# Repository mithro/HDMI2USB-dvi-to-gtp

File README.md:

Circuit designs for allowing DVI/HDMI be received on the GTP transceivers
inside the Spartan 6 LXT series parts.

Based of the information in 
[Xilinx provided XAPP1007](http://www.xilinx.com/support/documentation/application_notes/xapp1077-phy-hdmi-rx-gtp.pdf)

Designed for use with [HDMI2USB firmware](http://github.com/timvideos/HDMI2USB)
on the prototype version of the [Numato](http://numato.com/) HDMI2USB
"Conference" board.

# Files

Design is done in [KiCad](http://www.kicad-pcb.org/) using version
0.201408302346+5106~15~ubuntu12.04.1 (IE Subversion revision 5106 packaged on
2014/08/30 for Ubuntu Precise LTS - 12.04.01).

 * `dvi-to-gtp.pro`         - KiCad project.

  * `dvi-to-gtp.sch`         - Schematic
   * `dvi-to-gtp-cache.lib`  - Cache of components in use
   * `dvi-d.lib`             - DVI-D connector

  * `dvi-to-gtp.cmp`         - parts-to-module assignments file

  * `dvi-to-gtp.kicad_pcb`   - PCB Design
   * `dvi-d.pretty`          - DVI-D connector
   * `fp-lib-table`          - PCB library look up path

# Components

DVI-D connector used is;
 * Molex 74320-9004 - DVI-D, Dual Link, Panel Mount, Through Hole, Right Angle - [Datasheet](http://www.molex.com/pdm_docs/sd/743209004_sd.pdf)
 * Purchased from [Digikey](http://www.digikey.com/product-search/en?KeyWords=WM6095-ND&WT.z_header=search_go)

Passives;
 * [587-2658-1-ND](http://www.digikey.com/product-detail/en/LK21251R0K-T/587-2658-1-ND/2350029) - INDUCTOR MULTILAYER 1UH 0805
 * [1276-1443-1-ND](http://www.digikey.com/product-detail/en/CL05A104MP5NNNC/1276-1443-1-ND/3889529) - CAP CER 0.1UF 10V 20% X5R 0402
 * [RHM51.0CDCT-ND](http://www.digikey.com/product-detail/en/MCR01MRTF51R0/RHM51.0CDCT-ND/2796435) - RES 51 OHM 1/16W 1% 0402 SMD

# License

Copyright 2014 Tim "mithro" Ansell

Licensed under the Apache License, Version 2.0 (the "License");
you may not use this file except in compliance with the License.
You may obtain a copy of the License at

    http://www.apache.org/licenses/LICENSE-2.0

Unless required by applicable law or agreed to in writing, software
distributed under the License is distributed on an "AS IS" BASIS,
WITHOUT WARRANTIES OR CONDITIONS OF ANY KIND, either express or implied.
See the License for the specific language governing permissions and
limitations under the License.

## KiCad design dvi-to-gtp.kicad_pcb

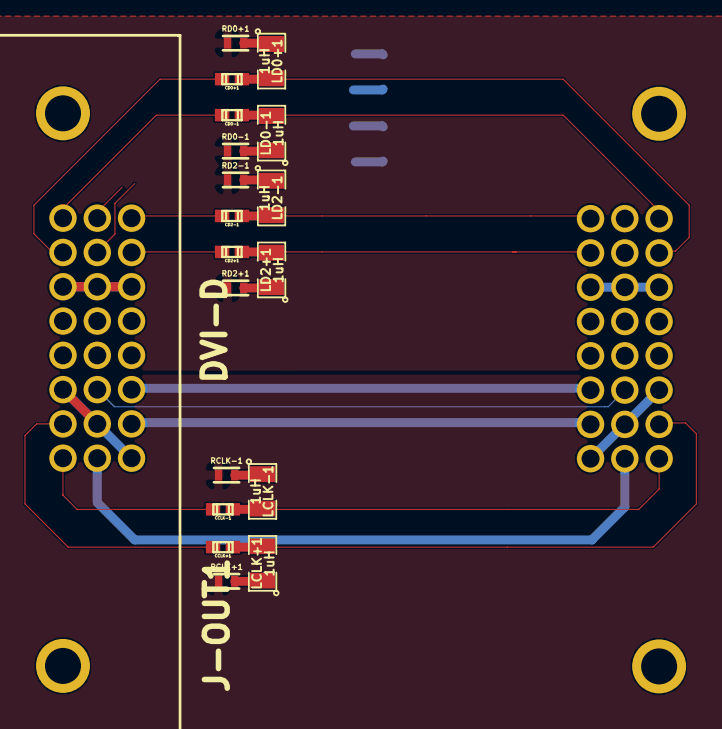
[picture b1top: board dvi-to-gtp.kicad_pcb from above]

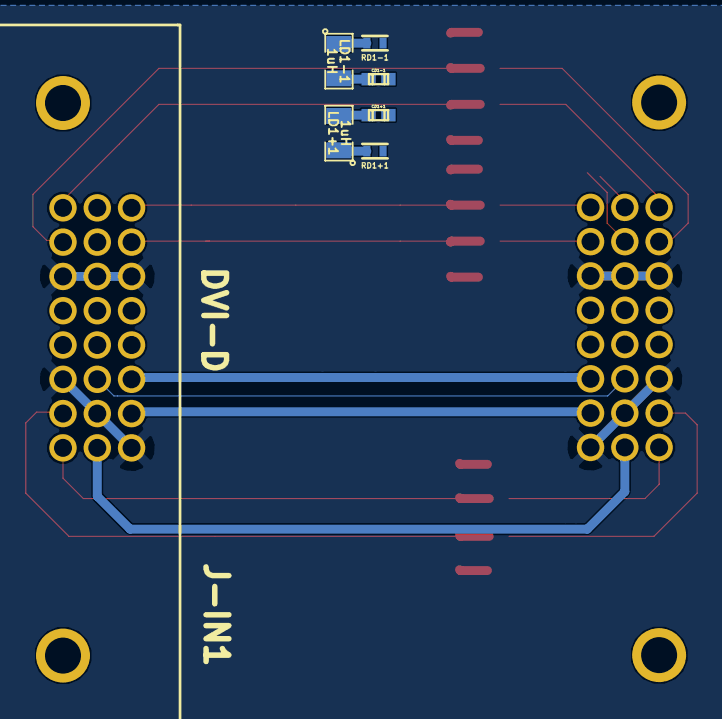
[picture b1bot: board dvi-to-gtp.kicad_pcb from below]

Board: 2 copper layers, 26 parts (7 on the bottom side), 30 nets.

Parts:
CCLK+1: 100nF; c_0402
CCLK-1: 100nF; c_0402
CD0+1, CD0-1, CD1+1, CD1-1, CD2+1, CD2-1: 100nF; c_0402
J-IN1: DVI-D; dvi-d
J-OUT1: DVI-D; dvi-d
LCLK+1: 1uH; SMD-0805
LCLK-1: 1uH; SMD-0805
LD0+1, LD0-1, LD1+1, LD1-1, LD2+1, LD2-1: 1uH; SMD-0805
RCLK+1: 51; R_0402
RCLK-1: 51; R_0402
RD0+1, RD0-1, RD1+1, RD1-1, RD2+1, RD2-1: 51; R_0402

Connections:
3V3: RCLK+1.1, RCLK-1.1, RD0+1.1, RD0-1.1, RD1+1.1, RD1-1.1, RD2+1.1, RD2-1.1
/+5V: J-IN1.14, J-OUT1.14
/HPD: J-IN1.16, J-OUT1.16
/IN-CLK+: CCLK+1.2, J-IN1.23, LCLK+1.2
/IN-CLK-: CCLK-1.2, J-IN1.24, LCLK-1.2
/IN-D0+: CD0+1.2, J-IN1.18, LD0+1.2
/IN-D0-: CD0-1.2, J-IN1.17, LD0-1.2
/IN-D1+: CD1+1.2, J-IN1.10, LD1+1.2
/IN-D1-: CD1-1.2, J-IN1.9, LD1-1.2
/IN-D2+: CD2+1.2, J-IN1.2, LD2+1.2
/IN-D2-: CD2-1.2, J-IN1.1, LD2-1.2
/OUT-CLK+: CCLK+1.1, J-OUT1.23
/OUT-CLK-: CCLK-1.1, J-OUT1.24
/OUT-D0+: CD0+1.1, J-OUT1.18
/OUT-D0-: CD0-1.1, J-OUT1.17
/OUT-D1+: CD1+1.1, J-OUT1.10
/OUT-D1-: CD1-1.1, J-OUT1.9
/OUT-D2+: CD2+1.1, J-OUT1.2
/OUT-D2-: CD2-1.1, J-OUT1.1
/SCL: J-IN1.6, J-OUT1.6
/SDA: J-IN1.7, J-OUT1.7
GND: J-IN1.3, J-IN1.8, J-IN1.11, J-IN1.15, J-IN1.19, J-IN1.22, J-OUT1.3, J-OUT1.8, J-OUT1.11, J-OUT1.15, J-OUT1.19, J-OUT1.22
unnamed: LCLK+1.1, RCLK+1.2
unnamed: LCLK-1.1, RCLK-1.2
unnamed: LD0+1.1, RD0+1.2
unnamed: LD0-1.1, RD0-1.2
unnamed: LD1+1.1, RD1+1.2
unnamed: LD1-1.1, RD1-1.2
unnamed: LD2+1.1, RD2+1.2
unnamed: LD2-1.1, RD2-1.2

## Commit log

2014-09-07 Initial README and .gitignore file
2014-09-07 Start of a schematic.
